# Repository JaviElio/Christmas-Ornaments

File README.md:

View this project on [CADLAB.io](https://cadlab.io/project/1880). 

# Christmas-Ornaments
ESP8266 Christmas ornaments 

Based on this project:

	- Title:	ESP8266 Christmas Ornaments!
	- Author:	Sean Hodgins
	- Link:		https://www.instructables.com/id/ESP8266-Christmas-Ornaments/

FEATURES:

If front button of the ornament is pressed, a random song is played. Then, other ornaments plays a song too (within 5 min max.)

Every time the front button is pressed a counter in thinkSpesk.com is increased. Also, every 5 min. the counter is checked to know if a song must be played.

If the ornament could not reach a wifi AP, a captative portal is activated to configure a connection to different Wifi AP.

PICTURES:

TO IMPROVE:

Voltage regulator doesn't work if battery protection circuit is populated.

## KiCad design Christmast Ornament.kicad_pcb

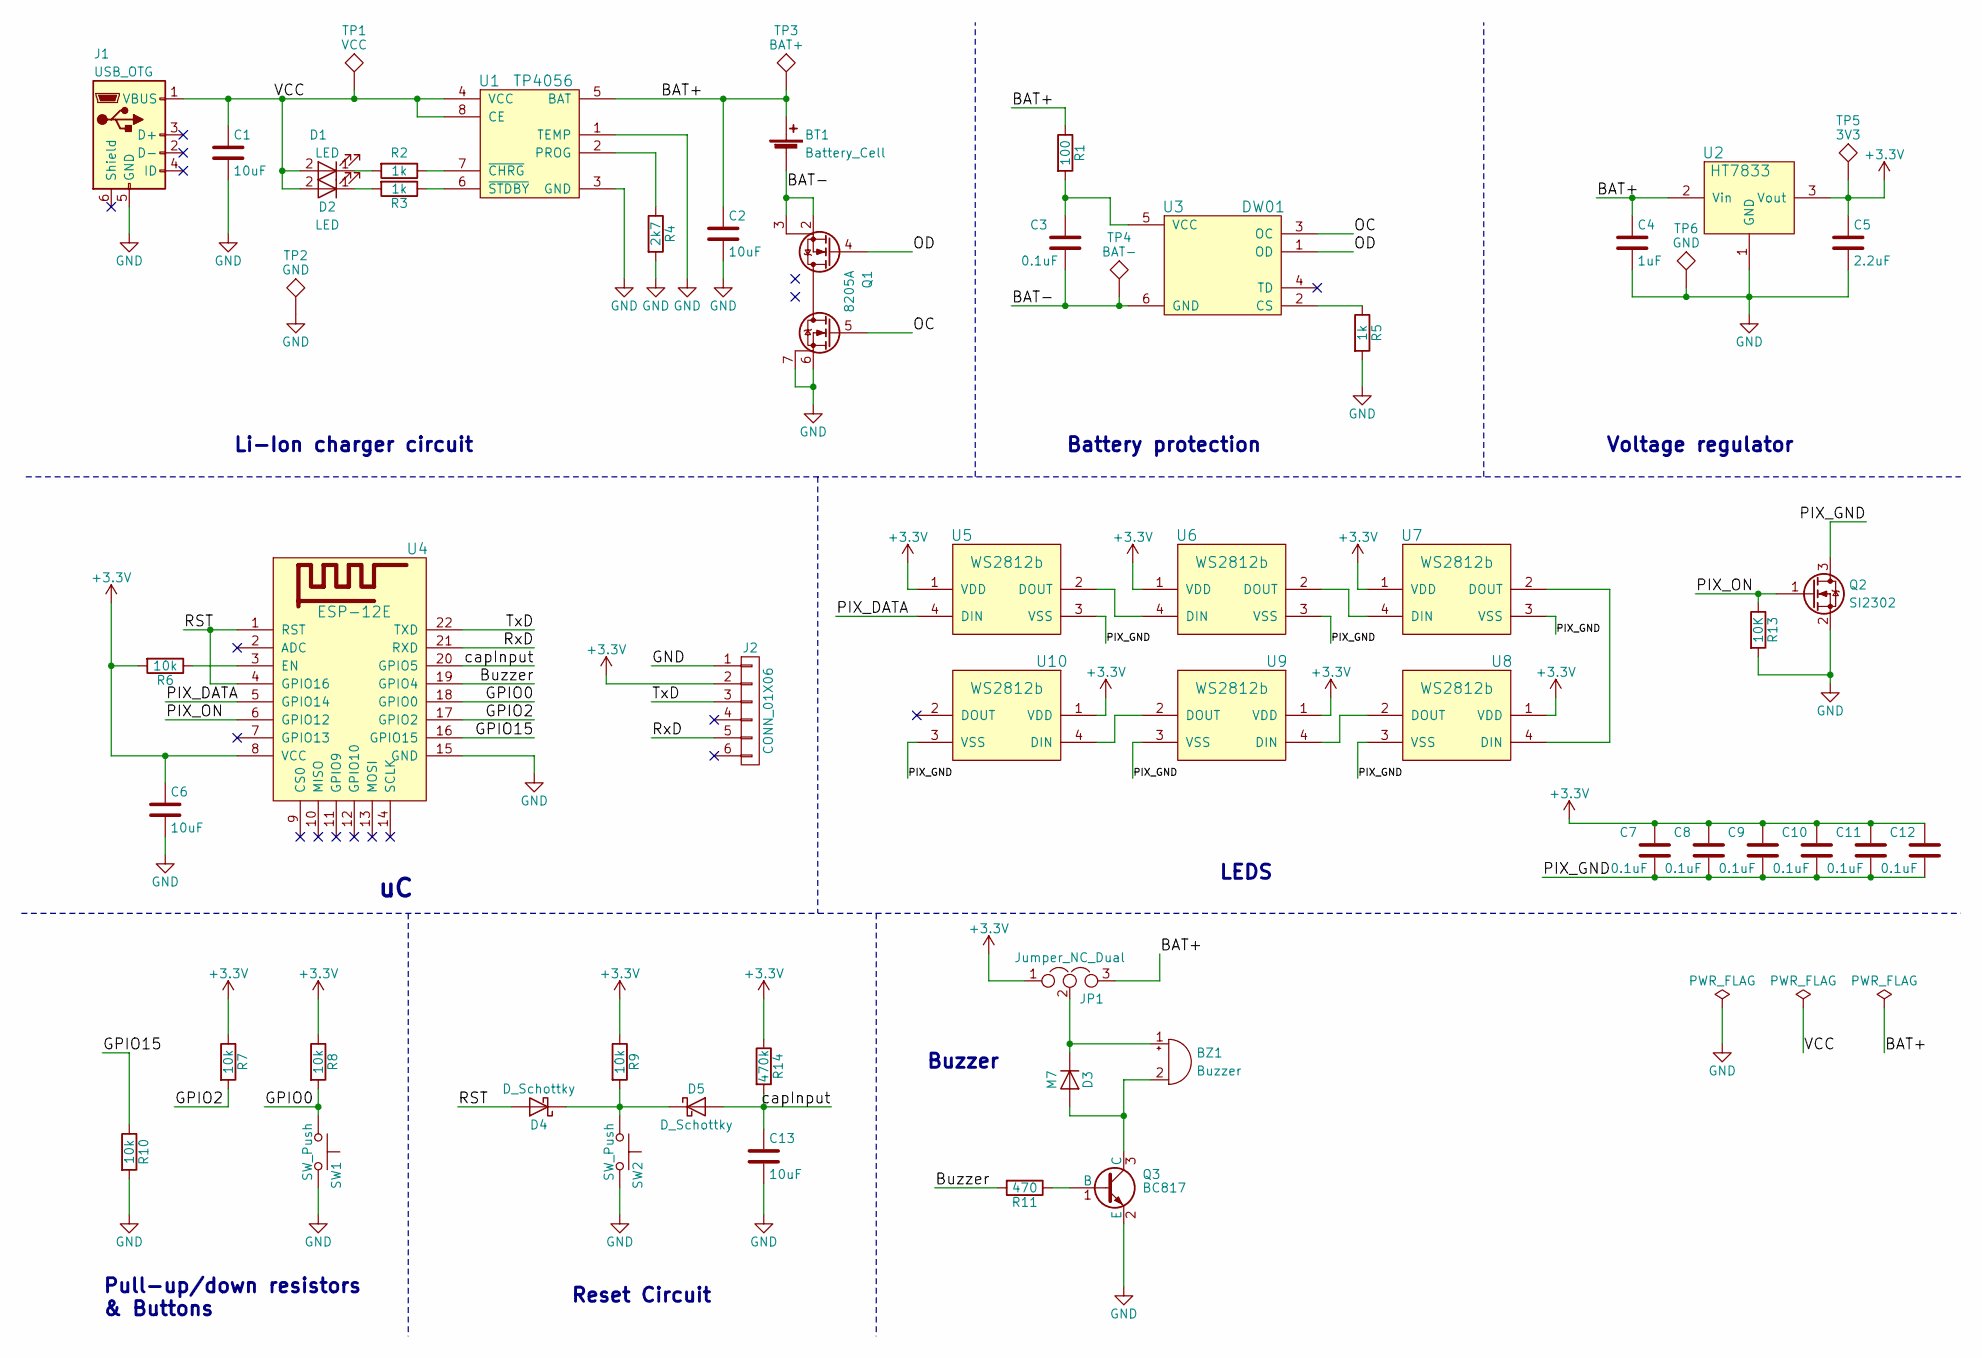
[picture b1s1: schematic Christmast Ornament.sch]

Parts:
BT1: Battery_Cell; 18650_SMD_Case
BZ1: Buzzer; Buzzer_8.5x8.5mm
C1, C2, C6, C13: 10uF; C_0805_HandSoldering
C3, C7, C8, C9, C10, C11, C12: 0.1uF; C_0805_HandSoldering
C4: 1uF; C_0805_HandSoldering
C5: 2.2uF; CP_Tantalum_Case-A_EIA-3216-18_Hand
D1, D2: LED; LED_0805
D3: M7; D_SMA_Handsoldering
D4, D5: D_Schottky; D_0805
J1: USB_OTG; MicroUSB
J2: CONN_01X06; Pin_Header_Straight_2x03_Pitch2.54mm_SMD
JP1: Jumper_NC_Dual; Jumper_2-NC
Q1: 8205A; TSSOP-8_4.4x3mm_Pitch0.65mm
Q2: SI2302; SOT-23_Handsoldering
Q3: BC817; SOT-23_Handsoldering
R1: 100; R_0805_HandSoldering
R2, R3, R5: 1k; R_0805_HandSoldering
R4: 2k7; R_0805_HandSoldering
R6, R7, R8, R9, R10: 10k; R_0805_HandSoldering
R11: 470; R_0805_HandSoldering
R13: 10K; R_0805_HandSoldering
R14: 470k; R_0805_HandSoldering
SW1, SW2: SW_Push; SW_SPST_SKQG
TP1: VCC; Measurement_Point_Square-SMD-Pad_Small
TP2, TP6: GND; Measurement_Point_Square-SMD-Pad_Small
TP3: BAT+; Measurement_Point_Square-SMD-Pad_Small
TP4: BAT-; Measurement_Point_Square-SMD-Pad_Small
TP5: 3V3; Measurement_Point_Square-SMD-Pad_Small
U1: TP4056; SOIC-8_3.9x4.9mm_Pitch1.27mm
U2: HT7833; SOT89-3_Housing_Handsoldering
U3: DW01; SOT-23-6_Handsoldering
U4: ESP-12E; ESP-12E_SMD
U5, U6, U7, U8, U9, U10: WS2812b; LED_WS2812B-PLCC4

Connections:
+3V3: C5.1, C6.1, C7.1, C8.1, C9.1, C10.1, C11.1, C12.1, J2.2, JP1.1, R6.2, R7.1, R8.1, R9.1, R14.1, TP5.1, U2.3 (Vout), U4.8 (VCC), U5.1 (VDD), U6.1 (VDD), U7.1 (VDD), U8.1 (VDD), U9.1 (VDD), U10.1 (VDD)
/BAT+: BT1.1 (+), C2.1, C4.1, JP1.3, R1.1, TP3.1, U1.5 (BAT), U2.2 (Vin)
/BAT-: BT1.2 (-), C3.2, Q1.2 (S1), Q1.3 (S1), TP4.1, U3.6 (GND)
/Buzzer: R11.2, U4.19 (GPIO4)
/GPIO0: R8.2, SW1.1, U4.18 (GPIO0)
/GPIO2: R7.2, U4.17 (GPIO2)
/GPIO15: R10.1, U4.16 (GPIO15)
/OC: Q1.5 (G2), U3.3 (OC)
/OD: Q1.4 (G1), U3.1 (OD)
/PIX_DATA: U4.5 (GPIO14), U5.4 (DIN)
/PIX_GND: C7.2, C8.2, C9.2, C10.2, C11.2, C12.2, Q2.3 (D), U5.3 (VSS), U6.3 (VSS), U7.3 (VSS), U8.3 (VSS), U9.3 (VSS), U10.3 (VSS)
/PIX_ON: Q2.1 (G), R13.1, U4.6 (GPIO12)
/RST: D4.2 (A), U4.1 (RST), U4.4 (GPIO16)
/RxD: J2.5, U4.21 (RXD)
/TxD: J2.3, U4.22 (TXD)
/VCC: C1.1, D1.2 (A), D2.2 (A), J1.1 (VBUS), TP1.1, U1.4 (VCC), U1.8 (CE)
/capInput: C13.1, D5.2 (A), R14.2, U4.20 (GPIO5)
GND: C1.2, C2.2, C4.2, C5.2, C6.2, C13.2, J1.5 (GND), J2.1, Q1.6 (S2), Q1.7 (S2), Q2.2 (S), Q3.2 (E), R4.2, R5.2, R10.2, R13.2, SW1.2, SW2.2, TP2.1, TP6.1, U1.1 (TEMP), U1.3 (GND), U2.1 (GND), U4.15 (GND)
unnamed: BZ1.1 (-), D3.1 (K), JP1.2
unnamed: BZ1.2 (+), D3.2 (A), Q3.3 (C)
unnamed: C3.1, R1.2, U3.5 (VCC)
unnamed: D1.1 (K), R2.2
unnamed: D2.1 (K), R3.2
unnamed: D4.1 (K), D5.1 (K), R9.2, SW2.1
unnamed: Q3.1 (B), R11.1
unnamed: R2.1, U1.7 (~CHRG)
unnamed: R3.1, U1.6 (~STDBY)
unnamed: R4.1, U1.2 (PROG)
unnamed: R5.1, U3.2 (CS)
unnamed: R6.1, U4.3 (EN)
unnamed: U5.2 (DOUT), U6.4 (DIN)
unnamed: U6.2 (DOUT), U7.4 (DIN)
unnamed: U7.2 (DOUT), U8.4 (DIN)
unnamed: U8.2 (DOUT), U9.4 (DIN)
unnamed: U9.2 (DOUT), U10.4 (DIN)

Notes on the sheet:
Li-Ion charger circuit
Battery protection
Voltage regulator
LEDS
Buzzer
Pull-up/down resistors & Buttons
Reset Circuit

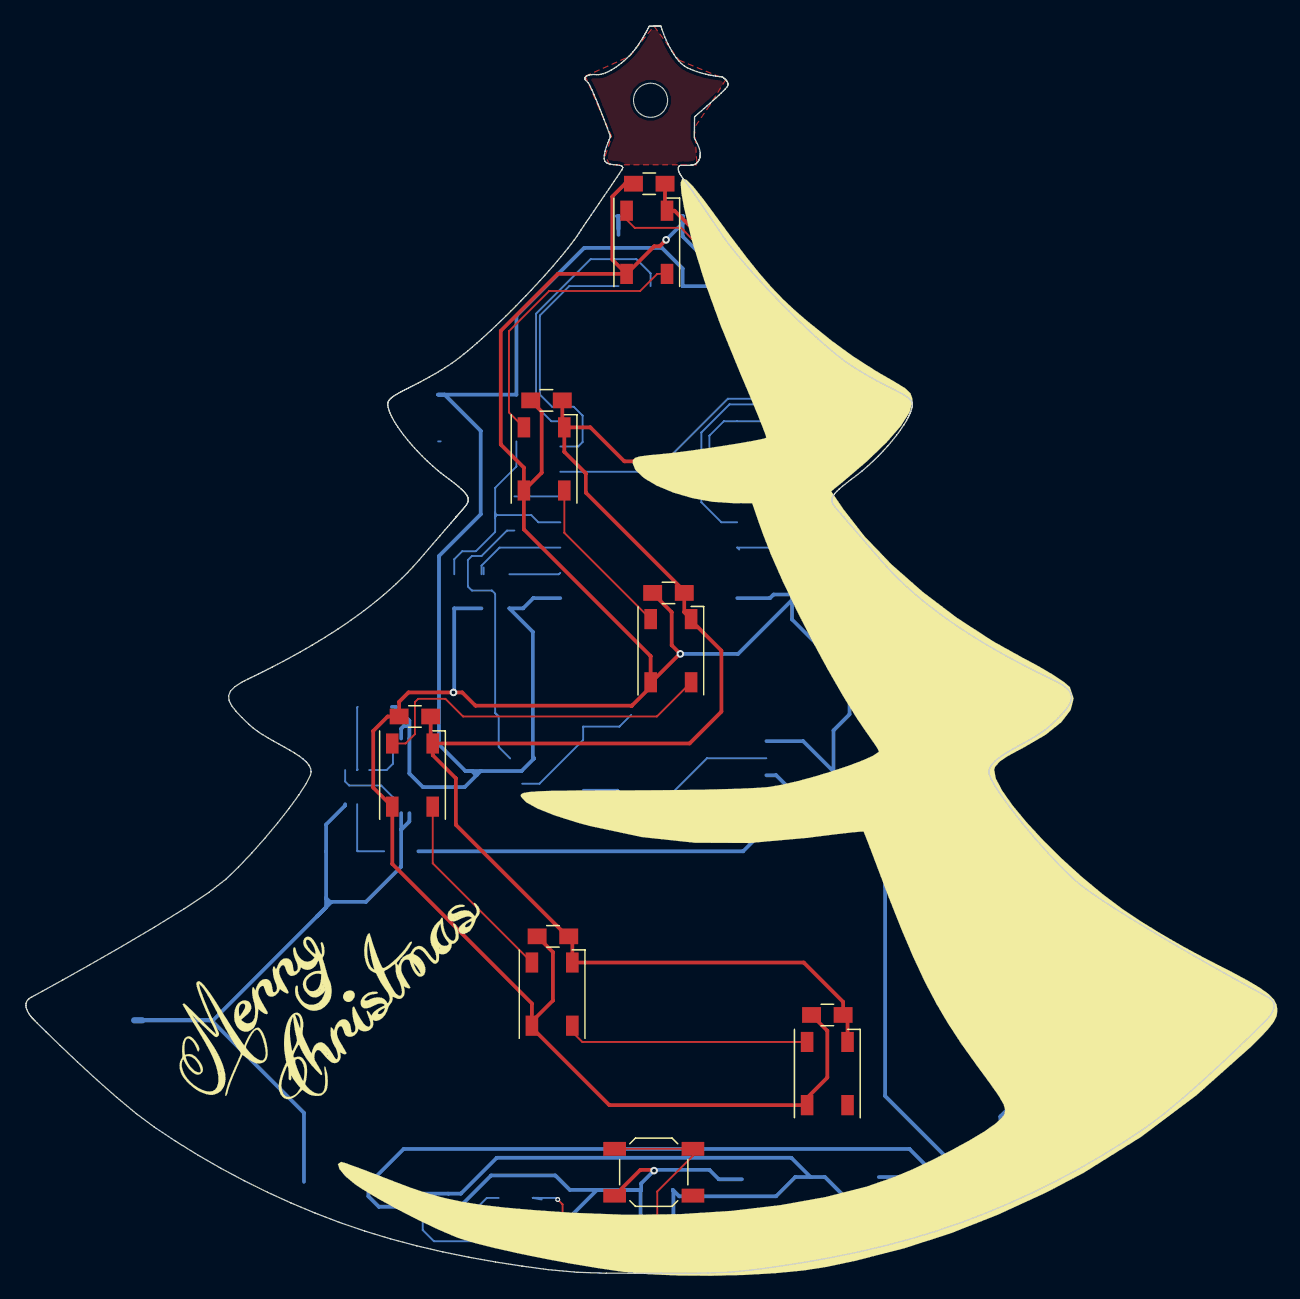
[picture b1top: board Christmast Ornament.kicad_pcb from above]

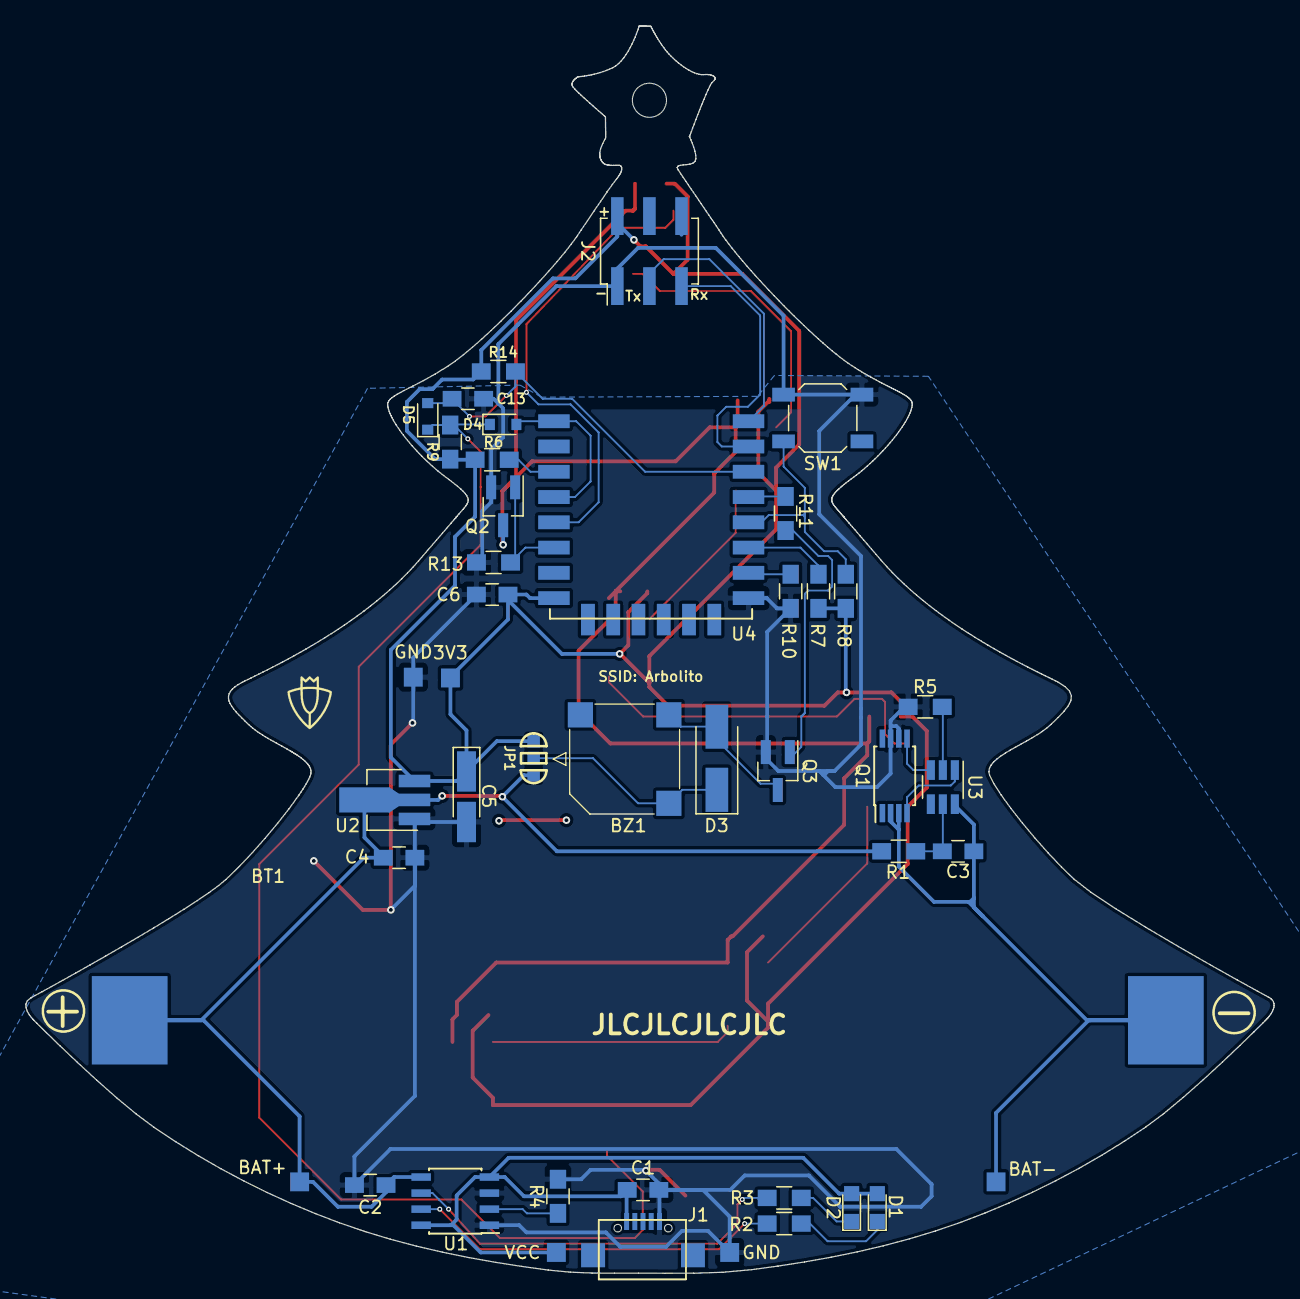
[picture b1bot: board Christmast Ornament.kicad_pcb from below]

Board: 2 copper layers, 98.8 x 98.7 mm, 57 parts (44 on the bottom side), 35 nets.

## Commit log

2018-05-26 First upload
2018-05-26 Buzzer circuit and test points
2018-06-01 First attempt to distribute components
2018-06-08 PCB routed
2018-06-13 PCB designed and gerbers
2018-07-24 TP4056 ground connection fixed
2018-07-25 8205A footprint changed
2018-08-15 Components added to reset button
2018-08-15 First firmware upload
2018-08-15 capInput routed and R12 deleted
2018-08-17 Gerber files generated
2018-08-20 SSID and password added to back silkscreen
2018-08-25 Status led indicatis if config portal is active
2018-08-25 Silkscreen text changed
2018-08-25 Mute off
2018-09-20 Minor changes
2018-09-25 Added text for the custemer Id
2018-09-25 changes in tick() function
2018-10-09 Schematic pdf uploaded
2018-10-16 Built in led blinks when captative portal is active
2018-11-13 Upload some pictures
2018-11-13 Readme updted
2019-06-17 Backlink to CADLAB.io has been added.
